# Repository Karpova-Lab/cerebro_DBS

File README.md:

# CerebroDBS Wireless Deep Brain Stimulation System

This repository contains all files needed to replicate a wireless DBS system that was developed in the [Karpova Lab ](https://www.janelia.org/lab/karpova-lab) at HHMI's Janelia Research Campus.

## Licenses
The MIT License (MIT)

Copyright (c) 2018 Andy Lustig

Permission is hereby granted, free of charge, to any person obtaining a copy of this software and associated documentation files (the “Software”), to deal in the Software without restriction, including without limitation the rights to use, copy, modify, merge, publish, distribute, sublicense, and/or sell copies of the Software, and to permit persons to whom the Software is furnished to do so, subject to the following conditions:

The above copyright notice and this permission notice shall be included in all copies or substantial portions of the Software.

THE SOFTWARE IS PROVIDED “AS IS”, WITHOUT WARRANTY OF ANY KIND, EXPRESS OR IMPLIED, INCLUDING BUT NOT LIMITED TO THE WARRANTIES OF MERCHANTABILITY, FITNESS FOR A PARTICULAR PURPOSE AND NONINFRINGEMENT. IN NO EVENT SHALL THE AUTHORS OR COPYRIGHT HOLDERS BE LIABLE FOR ANY CLAIM, DAMAGES OR OTHER LIABILITY, WHETHER IN AN ACTION OF CONTRACT, TORT OR OTHERWISE, ARISING FROM, OUT OF OR IN CONNECTION WITH THE SOFTWARE OR THE USE OR OTHER DEALINGS IN THE SOFTWARE.

      <br /><span xmlns:dct="http://purl.org/dc/terms/" property="dct:title">Cerebro Wireless Optogenetics System</span> by
      <a xmlns:cc="http://creativecommons.org/ns#" href="https://www.janelia.org/lab/karpova-lab" property="cc:attributionName" rel="cc:attributionURL">
      Andy Lustig </a> is licensed under a  <a rel="license" href="http://creativecommons.org/licenses/by-sa/4.0/">Creative Commons Attribution-ShareAlike 4.0 International License</a>

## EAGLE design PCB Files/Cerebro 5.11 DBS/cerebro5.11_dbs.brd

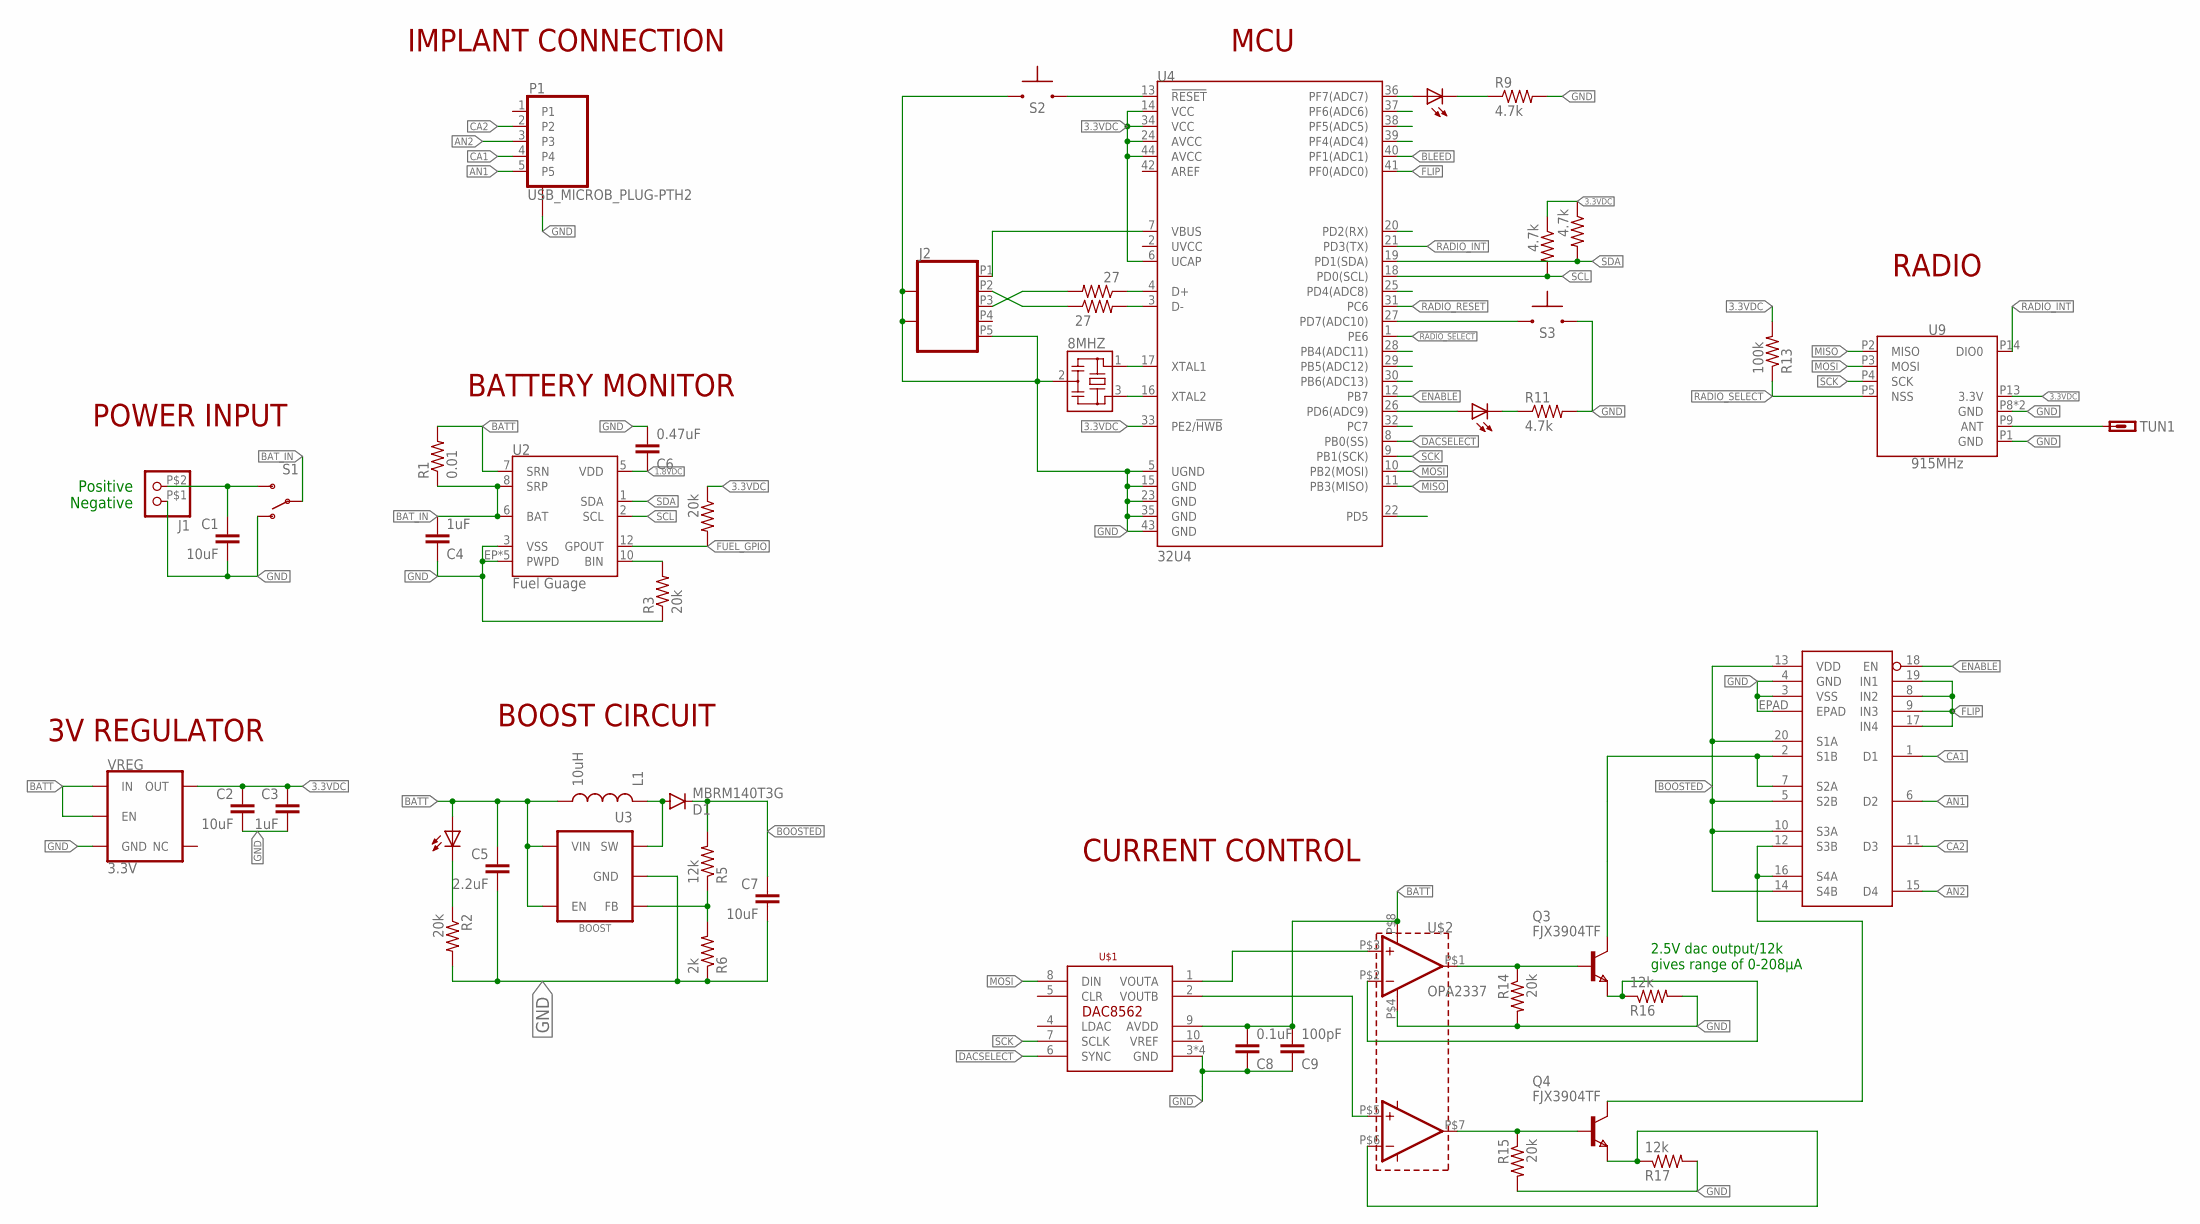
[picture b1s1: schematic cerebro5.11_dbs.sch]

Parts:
8MHZ: RESONATOR_CSTCE_V; CSTCE_V
C1, C2, C7: 10uF; 0805
C3, C4: 1uF; 0805
C5: 2.2uF; 0805
C6: 0.47uF; 0805
C8: 0.1uF; 0805
C9: 100pF; 0805
D1: MBRM140T3G; POWERMITE
J1: JST_2PINMICRO; MICRO_LOCK_2PIN
J2: USB_MICRO_SOCKET_HORZ_REINFORCED; USB_HORZ_REINFORCED_MICRO
L1: 10uH; 1812
LED1: RED; CHIP-LED0603
LED2, LED3: YLW; CHIP-LED0603
P1: USB_MICROB_PLUG-PTH2; MICRO-B-TH
Q3, Q4: FJX3904TF; SOT323
R1: 0.01; 1206
R2, R3, R4, R14, R15: 20k; 0603-RES
R5: 12k; 0805
R6: 2k; 0603-RES
R7, R8: 27; 0603-RES
R9, R10, R11, R12: 4.7k; 0603-RES
R13: 100k; 0603-RES
R16, R17: 12k; 0603-RES
S1: SWITCH-SPDTREINFORCED_SMD; SWITCH-SPDT-SMD-REINFORCED
S2, S3: SWITCH-MOMENTARY-NO; SWITCH_MOMENTARY_XS
TUN1: ANTENNA; 1X01
U2: Fuel Guage; PDSO-N12
U3: BOOST; SOT23-5
U4: 32U4; QFN-44-NOPAD
U9: 915MHz; RFM69HCW-XXXS2
U$1: DAC8562; WSON-10
U$2: OPA2337; SOT23-8
U$3: ADG1434; LFCSP_5X5
VREG: 3.3V; SOT23-5

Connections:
1.8VDC: C6.1, U2.5 (VDD)
3.3VDC: C2.1, C3.1, R4.1, R10.1, R12.1, R13.2, U4.6 (UCAP), U4.14 (VCC), U4.24 (AVCC), U4.33 (PE2/!HWB), U4.34 (VCC), U4.44 (AVCC), U9.P13 (3.3V), VREG.5 (OUT)
AN1: P1.5, U$3.6 (D2)
AN2: P1.3, U$3.15 (D4)
BATT: C5.1, C8.2, C9.2, L1.P$2 (2), L1.P$4 (2), LED1.A, R1.2, U2.7 (SRN), U3.4 (EN), U3.5 (VIN), U$1.9 (AVDD), U$2.P$8 (V+), VREG.1 (IN), VREG.3 (EN)
BAT_IN: C4.2, R1.1, S1.2, U2.6 (BAT), U2.8 (SRP)
BLEED: U4.40 (PF1(ADC1))
BOOSTED: C7.1, D1.CATHODE (C), R5.2, U$3.5 (S2B), U$3.10 (S3A), U$3.13 (VDD), U$3.14 (S4B), U$3.20 (S1A)
CA1: P1.4, U$3.1 (D1)
CA2: P1.2, U$3.11 (D3)
DACSELECT: U4.8 (PB0(SS)), U$1.6 (SYNC)
ENABLE: U4.12 (PB7), U$3.18 (EN)
FLIP: U4.41 (PF0(ADC0)), U$3.8 (IN2), U$3.9 (IN3), U$3.17 (IN4), U$3.19 (IN1)
FUEL_GPIO: R4.2, U2.12 (GPOUT)
GND: 8MHZ.2, C1.2, C2.2, C3.2, C4.1, C5.2, C6.2, C7.2, C8.1, C9.1, J1.P$1 (1), J2.G1, J2.G2, J2.P5, J2.P$1, J2.P$2, P1.P$1 (GND_PINS), P1.P$2 (GND_PINS), R2.2, R3.1, R6.1, R9.2, R11.2, R14.2, R15.2, R16.2, R17.2, S1.1 (O), S2.P$1 (1), S3.P$2 (2), U2.3 (VSS), U2.EP (PWPD), U2.EP1 (PWPD), U2.EP2 (PWPD), U2.EP3 (PWPD), U2.EP4 (PWPD), U3.2 (GND), U4.5 (UGND), U4.15 (GND), U4.23 (GND), U4.35 (GND), U4.43 (GND), U9.P1 (GND), U9.P8 (GND), U9.P10 (GND), U$1.3 (GND), U$1.G1 (GND), U$1.G2 (GND), U$1.G3 (GND), U$2.P$4 (V-), U$3.3 (VSS), U$3.4 (GND), U$3.EPAD, VREG.2 (GND)
MISO: U4.11 (PB3(MISO)), U9.P2 (MISO)
MOSI: U4.10 (PB2(MOSI)), U9.P3 (MOSI), U$1.8 (DIN)
unnamed: Q3.2 (B), R14.1, U$2.P$1 (OUTA)
unnamed: Q4.2 (B), R15.1, U$2.P$7 (OUTB)
unnamed: Q4.3 (E), R17.1, U$2.P$6 (INB-)
unnamed: C1.1, J1.P$2 (2), S1.3 (S)
unnamed: Q3.3 (E), R16.1, U$2.P$2 (INA-)
unnamed: LED1.C, R2.1
unnamed: R5.1, R6.2, U3.3 (FB)
unnamed: 8MHZ.1, U4.17 (XTAL1)
unnamed: 8MHZ.3, U4.16 (XTAL2)
unnamed: J2.P1, U4.7 (VBUS)
unnamed: D1.ANODE (A), L1.P$1 (1), L1.P$3 (1), U3.1 (SW)
unnamed: R7.1, U4.4 (D+)
unnamed: R8.2, U4.3 (D-)
unnamed: J2.P3, R7.2
unnamed: J2.P2, R8.1
unnamed: LED3.C, R11.1
unnamed: S3.P$1 (1), U4.27 (PD7(ADC10))
unnamed: TUN1.1, U9.P9 (ANT)
unnamed: LED2.C, R9.1
unnamed: LED2.A, U4.36 (PF7(ADC7))
unnamed: R3.2, U2.10 (BIN)
unnamed: Q4.1 (C), U$3.12 (S3B), U$3.16 (S4A)
unnamed: LED3.A, U4.26 (PD6(ADC9))
unnamed: U$1.1 (VOUTA), U$2.P$3 (INA+)
unnamed: U$1.2 (VOUTB), U$2.P$5 (INB+)
unnamed: Q3.1 (C), U$3.2 (S1B), U$3.7 (S2A)
RADIO_INT: U4.21 (PD3(TX)), U9.P14 (DIO0)
RADIO_RESET: U4.31 (PC6)
RADIO_SELECT: R13.1, U4.1 (PE6), U9.P5 (NSS)
RESET: S2.P$2 (2), U4.13 (!RESET)
SCK: U4.9 (PB1(SCK)), U9.P4 (SCK), U$1.7 (SCLK)
SCL: R10.2, U2.2 (SCL), U4.18 (PD0(SCL))
SDA: R12.2, U2.1 (SDA), U4.19 (PD1(SDA))

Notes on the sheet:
Positive
Negative
BOOST CIRCUIT
CURRENT CONTROL
RADIO
3V REGULATOR
BATTERY MONITOR
POWER INPUT
IMPLANT CONNECTION
MCU
2.5V dac output/12k gives range of 0-208µA

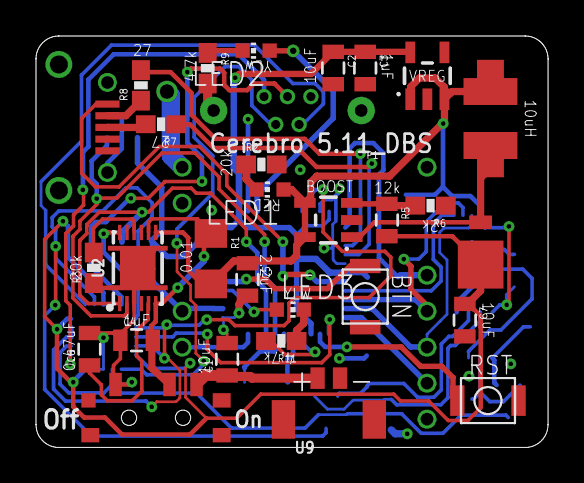
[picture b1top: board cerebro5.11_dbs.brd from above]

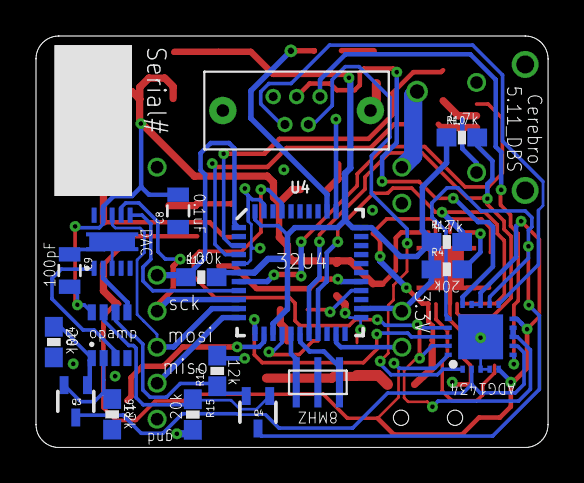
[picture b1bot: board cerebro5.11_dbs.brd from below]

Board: 2 copper layers, 28.4 x 22.9 mm, 49 parts (18 on the bottom side), 48 nets.

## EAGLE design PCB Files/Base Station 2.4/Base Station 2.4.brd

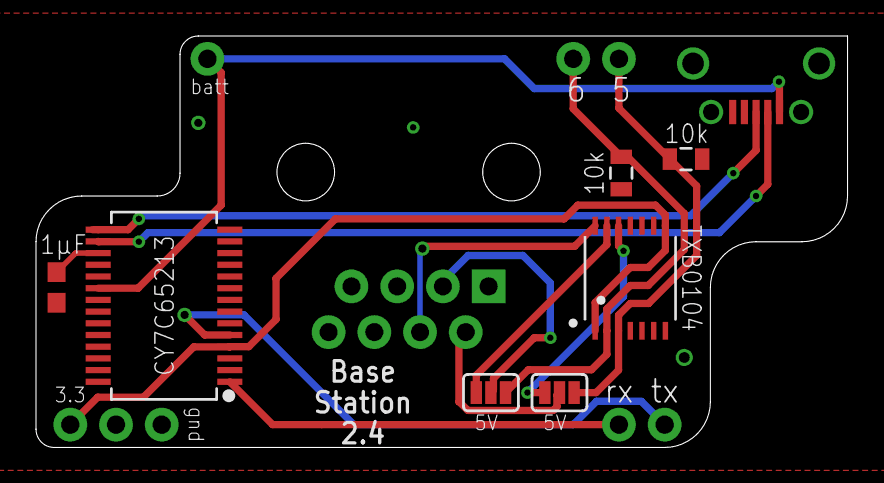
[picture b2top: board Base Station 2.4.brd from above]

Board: 2 copper layers, 45.1 x 22.9 mm, 13 parts (0 on the bottom side), 15 nets.

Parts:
C1: 1µF; 0603
J1: 1X01_NO_SILK
J2: 1X03_NO_SILK
JP1, JP2: 1X02_NO_SILK
R3, R4: 10k; 0805
SJ1, SJ2: SJ_3_PASTE2&3
U1: TXB0104; TSSOP14
U2: CY7C65213; SSOP28DB
U$3: RJ45; RJ45-8
U$4: USB_MICRO_SOCKET_HORZ_REINFORCED; USB_HORZ_REINFORCED_MICRO

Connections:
3.3VDC: J2.1, U1.1, U1.8, U2.4
5VDC: U1.14, U$3.4
BATT: J1.1, U2.20, U$4.P1
GND: C1.1, J2.3, R3.1, R4.1, U1.7, U2.7, U2.18, U2.21, U$3.5, U$4.G1, U$4.G2, U$4.P5, U$4.P$1, U$4.P$2
unnamed: JP1.1, U2.1
unnamed: JP1.2, U2.5
unnamed: U2.15, U$4.P3
unnamed: U2.16, U$4.P2
unnamed: C1.2, U2.17
unnamed: JP2.2, R4.2, SJ1.1, U1.2
unnamed: JP2.1, R3.2, SJ2.1, U1.3
unnamed: SJ2.3, U1.12
unnamed: SJ1.3, U1.13
OUT1: SJ1.2, U$3.3
OUT2: SJ2.2, U$3.2

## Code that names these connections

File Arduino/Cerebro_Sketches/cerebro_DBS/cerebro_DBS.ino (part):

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const uint8_t amberLED = A0; //32u4 pin 36
const uint8_t greenLED = 12; //32u4 pin 26
const uint8_t userBTN = 6; //32u4 pin 27
Electrode stim(&DDRB, &PORTB, 0,  //DAC SYNC pin is the chip select pin. p8/PB0/D17.
               &DDRB, &PORTB, 7,  //Switch enable pin. p12/PB7/D11
               &DDRF, &PORTF, 0); //Switch flip pin. p41/PF0/A5

uint8_t channel;
Radio radio(7,1); //slave select pin, interrupt pin
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
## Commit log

2018-12-13 cleanup qt folder
2018-12-13 Clear base monitor when "restart session" button is pressed. Increase the size of the COM port list box

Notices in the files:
Arduino/Cerebro_Sketches/cerebro_DBS/cerebro_DBS.ino:
Copyright (c) 2018 Andy S. Lustig
README.md:
CC BY-SA 4.0
parts and their libraries:
SparkFun-Connectors: Licensing: Creative Commons ShareAlike 4.0 International - https://creativecommons.org/licenses/by-sa/4.0
